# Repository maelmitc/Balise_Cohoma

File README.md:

# $${\color{black}Balise \space \color{black}Cohoma}$$

* CHARBONNIER Maëna
* MITCHEL Maël
* NGUYEN Denis
* SALOT Robin
* TESTUZ Lauriane

## $${\color{black}Présentation \space \color{black}du \space \color{black}{projet}}$$

Ce projet est en collaboration avec des deuxièmes années qui participent au projet Cohoma, pour l'armée de terre. Ce projet
est une compétition entre différentes écoles d'ingénieurs. Il consiste en la création d'un robot autonome s'adaptant à tout type de terrains. Ce robot doit lâcher des balises sur son chemin, elles ont pour but de le localiser. C'est ce sur quoi nous avons travaillé. 
   
Une LED RGB est utilisée afin de montrer le niveau de batterie de la balise (vert: pleine charge, jaune: à moitié chargée et rouge: déchargée). Quatre LEDs bleues sont également utilisées afin de déterminer le niveau de connexion Internet de la balise. Il y a également un capteur infrarouge qui permet de communiquer avec le rover afin d'allumer la batterie. Enfin, on utilise un convertisseur Buck-Boost, qui est une alimentation à découplage qui convertit une tension continue en une autre tension continue de plus faible ou de plus grande valeur, mais de polarité inverse.

## $${\color{black}Cahier \space \color{black}des \space \color{black}{charges}}$$

* Rendre visible le niveau de batteries de la balise (sur la balise).
* Rendre visible le niveau de réception WIFI de la balise (sur la balise).
* Communication infrarouge entre une télécommande et la balise.
* Communication infrarouge entre le rover et la balise dans le but d'allumer la balise après lors de l'éjection.
* Alimenter la balise.

## $${\color{black}Datasheet}$$

* [Buck / Boost ](https://www.farnell.com/datasheets/1999134.pdf)
* [Diode (Buck) (1N4148)](https://4donline.ihs.com/images/VipMasterIC/IC/DIOD/DIOD-S-A0001754954/DIOD-S-A0001754954-1.pdf?hkey=6D3A4C79FDBF58556ACFDE234799DDF0)
* [Diode Schottky (FSV340AF)](https://www.mouser.fr/datasheet/2/308/FSV340AF_D-1810142.pdf)
* [Capteur IR TFBS4650](https://www.vishay.com/docs/84672/tfbs4650.pdf)
* [Interface USB/UART(CY7C64225-28PVXCT)](https://www.mouser.fr/datasheet/2/196/CYPR_S_A0003298042_1-3003715.pdf)
* [Encodeur/Decodeur IrDA MCP2120-I/SL ](https://docs.rs-online.com/4edb/0900766b814ada76.pdf)
* [Quartz pour Encodeur/Decodeur IrDA ABLS-7.3728MHZ-20-B-3-H-T ](https://www.mouser.fr/datasheet/2/3/abls-1664338.pdf)
* [Récepteur IrDA TSOP75338TT](https://www.mouser.fr/datasheet/2/427/tsop753-1767096.pdf)
* [Emetteur IrDA VSML3710-GS18](https://www.mouser.fr/datasheet/2/427/vsml3710-1766511.pdf)
* [Processeur STM32L412KBT6](https://www.mouser.fr/datasheet/2/389/stm32l412c8-1851177.pdf)
* [Quartz pour STM32 ABLS-16.000MHZ-20-B-3-H-T:](https://www.mouser.fr/datasheet/2/3/abls-1664338.pdf)
* [Led bleu (niveau de réception) : MP008276]( https://www.farnell.com/datasheets/3497873.pdf)
* [Led RGB (niveau batterie) : 5988G10313F ](https://www.mouser.fr/datasheet/2/109/C18481B-2944388.pdf)
* [Driver de LED I2C : PCA9685PW,118 ]( https://www.mouser.fr/datasheet/2/302/PCA9685-1127478.pdf)

## $${\color{black}Déroulement \space \color{black}du \space \color{black}{projet}}$$

### Software :

L'objectif du logiciel développé est le traitement des données du routeur et de la batterie et la commande du <em>driver</em> LED. Le code a été développé en C. Le code est implémenté sur un processeur STM32 L412KBT6. En fonction des données reçues, le logiciel commande les LEDs, en particulier en fonction du niveau de batterie disponible. Le driver de LEDs, relié à quatre LEDs bleues et une LED RGB est connecté en I2C avec le processeur STM32.

* [Architecture <em>software</em>](Software/[CoHoMa]BeaconSoftwareArchitecture.drawio) (originale, modifiée depuis)
* [Code](Software/CHMBeaconB.zip)

#### Batterie
Selon le niveau de batterie calculé, 1 à 4 Blue LEDs sont allumées
* 75% : 4 LEDs activées
* 50% : 3 LEDs activées
* 25% : 2 LEDs activées
* 10% : 1 LED activée
On utilise une connexion I²C pour lier le STM32 au <em>driver</em> LED.

#### Routeur/IR
On utilise une LED RGB pour témoigner de la qualité de la connexion.
En fonctionnement normal, on utilise 3 couleurs : rouge (signal faible), vert (signal moyen), bleu (signal fort).

#### Problèmes rencontrés lors du développement :
* Longue lecture des fiches techniques des composants utilisés
* Recherche et étude d'un algorithme pour déterminer le niveau de batterie (SOC Algorithm)
* Lien entre la partie <em>hardware</em> et <em>software</em>, en particulier le lien avec la batterie/le niveau de charge

D'un point de vue personnel, je juge avoir sous-estimé la quantité de travail à fournir dans la partie <em>software</em>, trop importante pour une seule personne.

### Hardware - PCB Leds:

La version finale de mon [PCB](Hardware/PCB_LEDs/PCB_LEDs.kicad_sch_copie.kicad_pro).

#### Composants utilisés : 

Type de produit | Empreinte | Nombre 
--- | --- | ---
Driver de LEDs | Package_STO:TSSOP-28_4.4x9.7mm_P0.65mm | 1
LED bleue | LED_SMD:LED_0603_1608Metric_Pad1.05x0.95mm_HandSolder | 4 
LED RGB | LED_SMD:LED_Avago_PLCC6_3x2.8mm | 1
Résistance (100Ω et 150Ω)| Resistor_SMD:R_0603_1608Metric_Pad0.98x0.95mm_HandSolder | 7
Connecteur 01x05 | Connector_JST:JST_XH_B5B-XH-A_1x05_P2.50mm_Vertical | 1

#### Utilité des composants :

* Driver de LEDs : pilote les LEDs.
* LEDs bleues : montrent le niveau de connexion Wifi sur la balise. Plus le nombre de LEDs allumées est important, plus la connexion internet est bonne. 
* LED RGB : montre le niveau de batterie de la balise. Si la LED est verte, la balise est entièrement chargée ; jaune, à moitié chargée ; rouge, déchargée.
* Résistances : permettent de limiter le courant qui traverse les LEDs.
* Connecteur : permet de faire communiquer le driver de LEDs avec l’extérieur. Il est composé de cinq sorties : une d'alimentation et une de masse, mais également d'une sortie SDA (Serial Data Line), d'une sortie SCL (Serial Clock Line) et d'une sortie output enable, qui permet d’activer ou de désactiver les sorties de LEDs, en fonction des besoins.

#### Choix des résistances : 

Le driver de LEDs est alimenté par une tension de 5V. La tension maximum que peuvent recevoir les LEDs est d’environ 3V. Or, puisqu’on a un courant de 25 mA qui doit traverser les LEDs, on en conclut que la résistance qui doit être ajoutée afin de limiter la tension est de 100Ω. EN ce qui concerne la LED RGB, la diode rouge supporte une tension moins importante que les diodes jaune et verte. Sa résistance doit donc être supérieure à celles des diodes jaune et verte. C’est pourquoi, on ajoute une résistance de 150Ω.

#### Problèmes rencontrés lors de la fabrication de ce PCB : 

En ce qui concerne les LEDs bleues, il n'y a pas de problème, elles s'allument correctement. En revanche, cette partie comporte un principal problème : à cause d'une mauvaise connexion des pins de la LED RGB, on s'est rendu compte que seule la diode verte s'allume, les diodes jaune et rouge ne fonctionnent pas. Il faut prendre garde à ne pas se tromper entre l'anode et la cathode des diodes, pour éviter que l'erreur ne se reproduise. 

### Hardware - PCB IR :

La version finale de mon [PCB](Hardware/PCB_IR/cohoma.kicad_pro).

#### Composants utilisés : 

Type de produit | Empreinte | Nombre 
--- | --- | ---
Décodeur | Package_SO:SOIC-14_3.9x8.7mm_P1.27mm | 1
Récepteur Infrarouge | Package_SO:TSOP753TT (empreinte que nous avons créée) | 1
Quartz | Crystal:Crystal_SMD_7050-2Pin_7.0x5.0mm | 1
Condensateur (20 pF et 100 nF)| Capacitor_SMD:C_0603_1608Metric_Pad1.08x0.95mm_HandSolder | 3
Connecteur 01x03 | Connector_PinHeader_1.27mm:PinHeader_1x03_P1.27mm_Horizontal | 1 

Ce PCB se compose de plusieurs parties:

#### Récepteur IR:
Le récepteur IR reçoit un signal provenant d'un émetteur IR. Il renvoie alors RXIR à l'encodeur/décodeur dans le but que le signal soit décodé.
Afin d'éviter les fluctuations de tensions, il était recommandé par la datasheet, lorsque Vs<2.8 V d'utiliser une résistance et un condensateur. Ce n'est ici pas le cas, cependant, afin d'éviter tout risque, un condensateur de 100 nF a tout de même été ajouté.

#### Encodeur/Décodeur:
Dans le cadre de ce projet, ce composant a été utilisé uniquement comme un décodeur. Il reçoit RXIR, le décode et renvoie UART_RX au microcontrôleur (via le connecteur).
En effet, pour être compris par le microcontrôleur, le signal doit être en UART.

Les "BAUD" permettent de modifier la vitesse de transmission. Ils sont tous les trois mis à la masse ici, ce qui équivaut à les mettre à 0.

#### Quartz:
Le quartz sert d'horloge. Il est ici accompagné de deux condensateurs qui permettent de "lisser" afin que l'horloge soit vraiment régulière.

#### Difficultés rencontrées lors de la fabrication de ce PCB :
* Trouver les schematics correspondants au projet (pour plusieurs composants, elles n'existaient pas sur Kicad: il a donc été nécessaire de les trouver, les télécharger, puis les importer sur Kicad).
* La datasheet du quartz ne permettait pas de connaître la schematic associée, il fallait effectuer d'autres recherches.
* De même pour les empreintes de certains composants, il fallait alors trouver une empreinte très proche, ou bien créer l'empreinte dans certains cas.
* Rendre le PCB le plus petit possible tout en respectant une contrainte: les deux condensateurs associés au Quartz devaient être aussi proche que possible de ce dernier.
* Problèmes rencontrés lors de la soudure liés à une mauvaise empreinte ( qui a été corrigée sur la dernière version du PCB).

### Hardware - PCB Buck-Boost:

La version finale de notre [PCB](Hardware/PCB_BuckBoost/pcb_v3/pcb_v3.kicad_pro).

#### Composants utilisés : 

Type de produit | Empreinte | Nombre 
--- | --- | ---
Diode| Diode_SMD:D_SOD-123F | 1
Diode| Diode_SMD:D_SOD-323F | 1
PS1| Footprints_Balise:PS1 | 1
Régulateur Buck/Boost | Package_SO:SOIC-8-1EP_3.9x4.9mm_P1.27mm_EP2.29x3mm | 2
Condensateur polarisé (330 uF)| Capacitor_SMD:CP_Elec_10x10.5 | 2
Condensateur polarisé (100 uF)| Capacitor_SMD:CP_Elec_6.3x7.7 | 1
Condensateur polarisé (22 uF)| Capacitor_SMD:CP_Elec_5x5.4 | 1
Condensateur (2.2 uF, 1 uF et 0.47 nF)| Capacitor_SMD:C_0603_1608Metric_Pad1.08x0.95mm_HandSolder | 6
LED bleue | LED_SMD:LED_0603_1608Metric_Pad1.05x0.95mm_HandSolder | 4 
Inductance (100 uH)| Inductor_SMD:L_Wuerth_WE-PD-Typ-LS | 2
Résistance | Resistor_SMD:R_0603_1608Metric_Pad0.98x0.95mm_HandSolder | 11
Diode Schottky | Footprints_Balise:Diode_Schottky (empreinte créée)| 2
Connecteur 01x02 | Connector_JST:JST_XH_B2B-XH-A_1x02_P2.50mm_Vertical | 4

#### Utilité des composants
* LEDs bleues : témoignent du bon fonctionnement de l'alimentation
* Diodes / Diode Schottky : permettent les différents états de commutation du régulateur
* Régulateur à découpage : gère le découpage (via le rapport cyclique) de la tension en fonction des différents états. Les régulateurs sont au nombre de deux, chacun est monté différemment, permettant le passage au mode Buck ou Boost.
* PS1 : régule la tension

#### Choix des composants     
Les composants (autre que ceux imposés) ont été sélectionnés en fonction des datasheets des montages Buck et Boost et des composants passifs disponibles à l'ENSEA. Pour ce qui est des condensateurs, des condensateurs classiques ou polarisés ont été choisi en fonction de la valeur des capacités indiquées sur la datasheet (au dessus de 10 uF, on choisit un condensateur polarisé).

#### Explication du fonctionnement des régulateurs à découplage  
Un régulateur de découplage est un type de régulateur de tension qui utilise des composants électroniques commutés (transistors, inductances, condensateurs) pour convertir l'énergie de manière efficace. 

Régulation de la tension d'entrée : Le régulateur de découplage commence par réguler et contrôler la tension d'entrée, celle-ci pouvant être supérieure ou inférieure à la tension de sortie souhaitée, à l'aide de composants électroniques commutés.

Conversion d'énergie : L'énergie est efficacement convertie en utilisant un interrupteur électronique, généralement un transistor, pour commuter rapidement entre les états "on" et "off". Il est possible de réduire les pertes d'énergie et d'améliorer l'efficacité globale du régulateur grâce à cette commutation.

Stockage de l'énergie : Pendant la commutation, l'énergie est stockée dans une inductance (bobine) lors de l'état "on" de l'interrupteur et est libérée lors de l'état "off". Cela permet de réguler et de maintenir la tension de sortie constante malgré les variations de la tension d'entrée ou de la charge.

Filtrage : Le régulateur de découplage utilise également des condensateurs pour filtrer les fluctuations résiduelles de la tension de sortie et pour fournir une alimentation stable et régulée.

#### Difficultés rencontrées lors de la fabrication de ce PCB : 
* Repérer sur la datasheet les montages buck et boost qui correspondaient au projet.
* Choisir des empreintes des condensateurs et des inductances adaptées à la situations (exemple : condensateurs polarisés).
* Assigner (voire créer) les bonnes empreintes car elles n'étaient pas toujours disponibles sur Kicad.  
* Agencer les composants afin d'obtenir un PCB le plus petit possible.
* Placer les composants traversés par une forte tension de manière optimale (ils devaient être proches des régulateurs à découpage).
* Il fallait imposer un courant de sortie de 100 mA, ce qui n'était possible que si la balise était complète. Or, ce n'était pas le cas, puisque nous n'avions que le PCB. Nous avons donc dû rajouter deux résistances en parallèle à un condensateur polarisé.
* Choisir une largeur de piste suffisante en fonction du courant qui traversait les différents composants. 
* Augmenter le nombre de vias car ils ne fonctionnaient pas toujours.
* Certaines pastilles de cuivres n'étaient pas connectés à la masse, une erreur lors de la conception du PCB sur Kicad.

## $${\color{black}Impact \space \color{black}environnemental}$$

### $${\color{green}Expliquer \space \color{green}les \space \color{green}{critères} \space \color{green}de \space \color{green}choix \space \color{green}du \space \color{green}mode \space \color{green}d'alimentation \space \color{green}de \space \color{green}votre \space \color{green}{projet}}$$

Notre projet exigeait déjà un cahier des charges précis à respecter. En effet, la plupart des composants, y compris l'alimentation Buck-Boost, étaient imposés. Cependant, on peut tout de même se demander pourquoi c'est une alimentation à découpage qui à été choisie plutôt qu'une alimentation linéaire. En effet, l'alimentation à découpage possède un rendement bien plus élevé (et consomme donc moins d'énergie) que l'amplificateur linéaire grâce à son fonctionnement "alterné" entre différents états de commutations. Cette meilleure efficacité énergétique est principalement due à leur principe de fonctionnement différent. Dans un régulateur linéaire, la tension excédentaire est dissipée sous forme de chaleur par un transistor de régulation. Cela signifie que la différence de tension entre l'entrée et la sortie du régulateur est convertie en chaleur, ce qui entraîne une perte d'énergie importante. Par conséquent, les régulateurs linéaires ont généralement une efficacité relativement faible, en particulier lorsque la différence de tension entre l'entrée et la sortie est importante. 

En revanche, les régulateurs de découplage utilisent des composants électroniques commutés, tels que des transistors MOSFET et des inductances, pour réguler la tension de sortie. Ces composants commutent rapidement entre les états "on" et "off", ce qui permet de minimiser les pertes d'énergie. Lorsque le transistor est en état "on", il présente une résistance très faible, ce qui réduit les pertes de puissance. Lorsque le transistor est en état "off", l'inductance stocke l'énergie et la restitue lors de l'état "on" suivant, ce qui permet de maintenir une tension de sortie constante.En conséquence, les régulateurs de découplage ont une efficacité énergétique beaucoup plus élevée que les régulateurs linéaires. Une plus grande quantité d'énergie est transférée du côté de l'entrée vers le côté de la sortie sans être dissipée sous forme de chaleur. De plus, en raison du rapport cyclique, le transformateur à l'intérieur de l'alimentation peut être très petit, réalisant ainsi la miniaturisation de la taille de l'alimentation tout en permettant également l'utilisation normale de l'alimentation. 

Il est à noter que dans certains cas (dans d'autres projets par exemple), l'utilisation des régulateurs linéaire est préférable : 
* Moins sensible aux variations de la tension d'entrée,
* Coût moins élevé,
* Meilleure performance en terme de réduction de bruit et des interférences électromagnétique, 
* Moins complexe
* Réglage plus fin de la sortie.

### $${\color{green}Votre \space \color{green}projet \space \color{green}favorise-t-il \space \color{green}une \space \color{green}utilisation \space \color{green}judicieuse \space \color{green}et \space \color{green}rationnelle \space \color{green}de \space \color{green}l'énergie, \space \color{green}en \space \color{green}minimisant \space \color{green}{les}}$$

### $${\color{green}impacts \space \color{green}de \space \color{green}sa \space \color{green}production, \space \color{green}de \space \color{green}sa \space \color{green}distribution \space \color{green}et \space \color{green}de \space \color{green}sa \space \color{green}{consommation?}}$$
 
La plupart des composants étant imposés, nous avons eu peu de marge de manoeuvre. Nous avons donc porté une attention toute particulière à la taille des PCBs conçus. En effet, ces derniers devaient être les plus petits possibles, afin de ne pas gaspiller de matériaux. De plus, les PCBs ayant été réalisés sur place, leur impact environnemental dû aux transports était minime, les composants étant déjà à l'école.
 
Pour ce qui est des LEDs présentes sur le projet, elles ne s’allument que lorsque le module qui leur est associé est sollicité. Ainsi il n'y a pas d'énergie utilisée inutilement. De plus, nous nous sommes assurés qu’aucun composant ne consomme plus d’énergie que celle nécessaire à son bon fonctionnement.

Cependant, si l’on s’intéresse au projet de manière plus large, son impact est plus important que ce que nous avons décrit précédemment. En effet, plusieurs écoles sont en compétition dans la réalisation de ce projet pour ne sélectionner que le meilleur. L’impact aurait été moins important si une seule équipe d’ingénieurs professionnels s’en était chargée. Néanmoins, cette compétition entre écoles encourage chacun des participants à réaliser le projet le plus efficace et propre possible dans l’espoir d’être sélectionnés.

## $${\color{black}Conclusion}$$

Nous avons manqué de temps pour atteindre tous nos objectifs. Cependant, si nous pouvions donner des conseils à nos successeurs, nous dirions de :
 
* Bien lire les datasheet des composants, de façon à choisir des valeurs de résistances ou de condensateurs appropriées, par exemple. 
* Faire particulièrement attention aux empreintes, quitte à en créer, de façon à n'avoir aucun problème lors de la soudure.
* Faire particulièrement attention au sens des diodes, ne pas intervertir l'anode et la cathode, dans le cas ou le PCB en comporte.
* Faire attention à la largeur des pistes, en fonction du courant qui traverse les différents composants.

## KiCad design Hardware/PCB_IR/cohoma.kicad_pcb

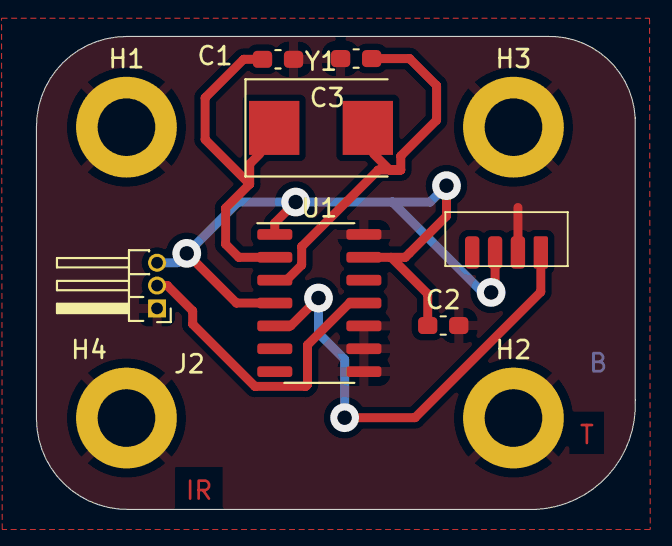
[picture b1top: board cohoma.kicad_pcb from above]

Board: 2 copper layers, 33.3 x 26.3 mm, 11 parts (0 on the bottom side), 5 nets.

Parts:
C1, C3: 20 pF; C_0603_1608Metric_Pad1.08x0.95mm_HandSolder
C2: 100 nF; C_0603_1608Metric_Pad1.08x0.95mm_HandSolder
H1: Mounting Hole 1; MountingHole_3.2mm_M3_DIN965_Pad
H2: Mounting Hole 2; MountingHole_3.2mm_M3_DIN965_Pad
H3: Mounting Hole 3; MountingHole_3.2mm_M3_DIN965_Pad
H4: Mounting Hole 4; MountingHole_3.2mm_M3_DIN965_Pad
J2: Conn_01x03; PinHeader_1x03_P1.27mm_Horizontal
U1: MCP2120-I/P; SOIC-14_3.9x8.7mm_P1.27mm
U2: TSOP75338WTT; TSOP753TT
Y1: ABLS-7.3728MHz-20-B-3-H-T; Crystal_SMD_7050-2Pin_7.0x5.0mm

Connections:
+3.3V: C2.1, J2.3, U1.1 (VDD), U1.4 (*RESET), U1.13 (EN)
GND: C1.2, C2.2, C3.2, H1.1, H2.1, H3.1, H4.1, J2.1, U1.8 (BAUD2), U1.9 (BAUD1), U1.10 (BAUD0), U1.14 (VSS)
Q_IN: C1.1, U1.2 (OSC1/CLKIN), Y1.1
Q_OUT: C3.1, U1.3 (OSC2), Y1.2
UART_RX: J2.2, U1.11 (RX)

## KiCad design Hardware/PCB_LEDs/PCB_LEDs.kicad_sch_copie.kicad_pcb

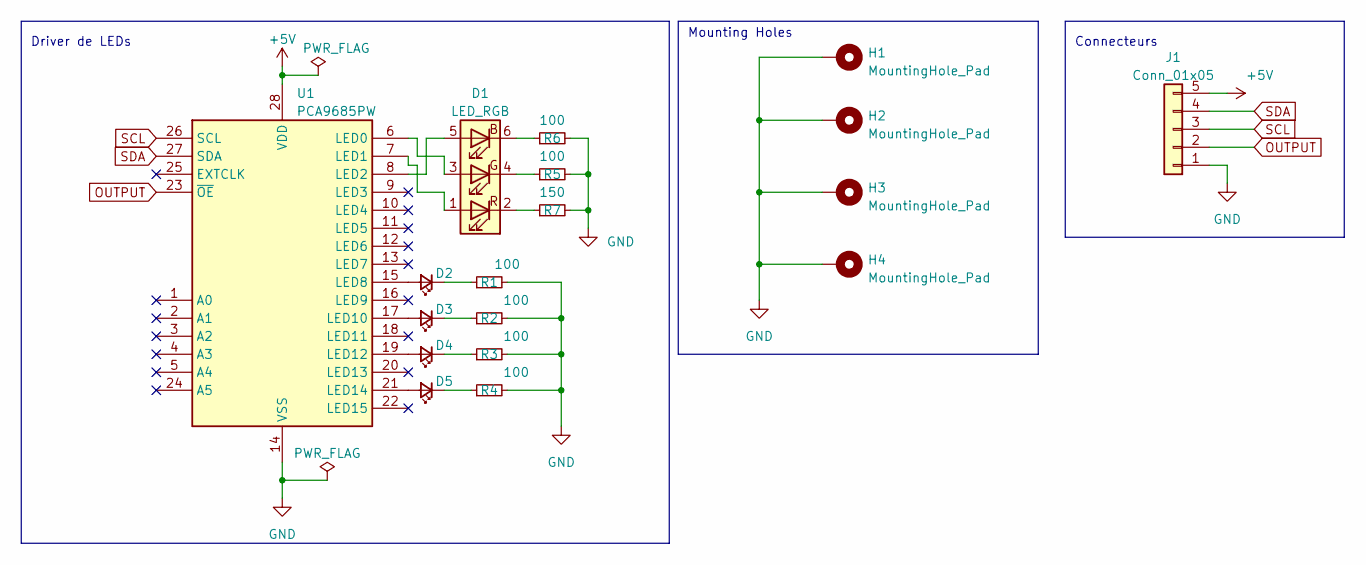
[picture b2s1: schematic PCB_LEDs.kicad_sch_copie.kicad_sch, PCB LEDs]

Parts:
D1: LED_RGB; LED_Avago_PLCC6_3x2.8mm
D2: LED_1; LED_0603_1608Metric_Pad1.05x0.95mm_HandSolder
D3: LED_2; LED_0603_1608Metric_Pad1.05x0.95mm_HandSolder
D4: LED_3; LED_0603_1608Metric_Pad1.05x0.95mm_HandSolder
D5: LED_4; LED_0603_1608Metric_Pad1.05x0.95mm_HandSolder
H1, H2, H3, H4: MountingHole_Pad; MountingHole_3.2mm_M3_DIN965_Pad
J1: Conn_01x05; JST_XH_B5B-XH-A_1x05_P2.50mm_Vertical
R1, R2, R3, R4, R5, R6: 100; R_0603_1608Metric_Pad0.98x0.95mm_HandSolder
R7: 150; R_0603_1608Metric_Pad0.98x0.95mm_HandSolder
U1: PCA9685PW; TSSOP-28_4.4x9.7mm_P0.65mm

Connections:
+5V: J1.5, U1.28 (VDD)
GND: H1.1, H2.1, H3.1, H4.1, J1.1, R1.2, R2.2, R3.2, R4.2, R5.2, R6.2, R7.2, U1.14 (VSS)
unnamed: D1.5 (BA), U1.8 (LED2)
unnamed: D1.4 (GK), R5.1
unnamed: D1.6, R6.1
unnamed: D1.1 (RA), U1.7 (LED1)
unnamed: D1.2 (RK), R7.1
unnamed: D2.2 (A), U1.15 (LED8)
unnamed: D2.1 (K), R1.1
unnamed: D3.2 (A), U1.17 (LED10)
unnamed: D3.1 (K), R2.1
unnamed: D4.2 (A), U1.19 (LED12)
unnamed: D4.1 (K), R3.1
unnamed: D5.2 (A), U1.21 (LED14)
unnamed: D5.1 (K), R4.1
unnamed: D1.3 (GK), U1.6 (LED0)
OUTPUT: J1.2, U1.23 (~OE)
SCL: J1.3, U1.26 (SCL)
SDA: J1.4, U1.27 (SDA)

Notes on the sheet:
Connecteurs
Mounting Holes
Driver de LEDs

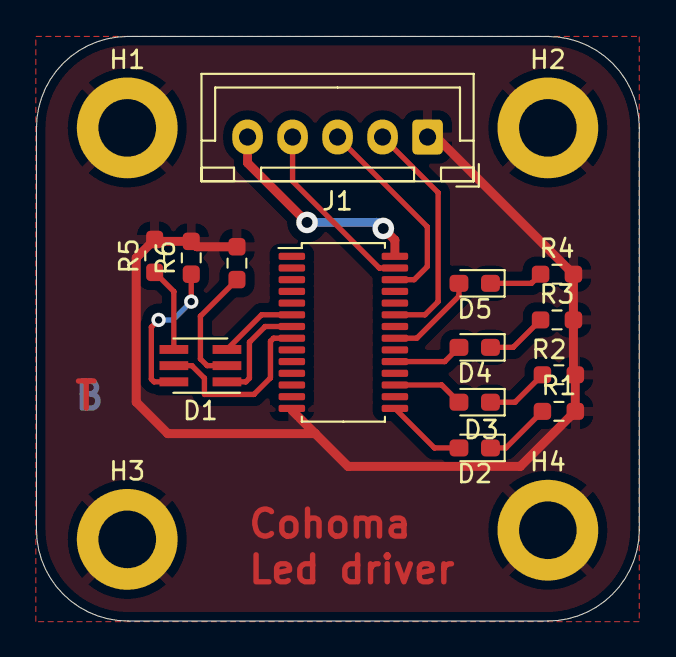
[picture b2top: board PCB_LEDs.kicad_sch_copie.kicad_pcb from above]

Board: 2 copper layers, 33.5 x 32.5 mm, 18 parts (0 on the bottom side), 19 nets.

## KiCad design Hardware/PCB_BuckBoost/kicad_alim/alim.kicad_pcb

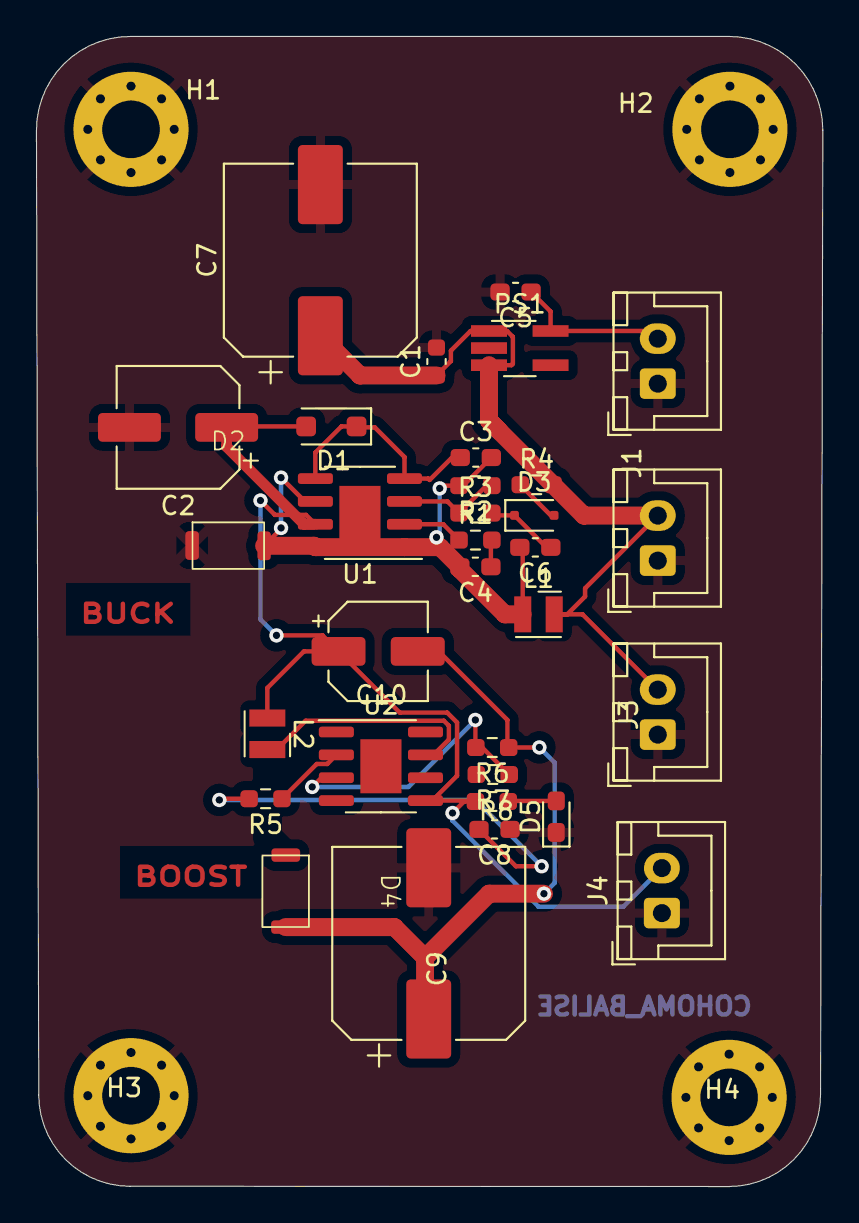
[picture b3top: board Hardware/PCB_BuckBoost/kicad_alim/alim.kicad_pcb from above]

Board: 2 copper layers, 43.7 x 63.9 mm, 36 parts (0 on the bottom side), 16 nets.

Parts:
C1: 0.47u; C_0603_1608Metric
C2: 100uF; CP_Elec_6.3x7.7
C3: 2.2 µF; C_0603_1608Metric_Pad1.08x0.95mm_HandSolder
C4, C6: 1 µF; C_0603_1608Metric_Pad1.08x0.95mm_HandSolder
C5: 0.47u; C_0603_1608Metric_Pad1.08x0.95mm_HandSolder
C7: 330uF; CP_Elec_10x10.5
C8: 1µF; C_0603_1608Metric_Pad1.08x0.95mm_HandSolder
C9: 470uF; CP_Elec_10x10.5
C10: 22uF; CP_Elec_5x5.4
D1: 1N4148; D_SOD-123F
D2, D4: FSV330AF; Diode_Shottky (copy)
D3: 1N4148; D_SOD-323F
D5: LED; LED_0603_1608Metric_Pad1.05x0.95mm_HandSolder
H1, H2, H3, H4: MountingHole_Pad; MountingHole_3.2mm_M3_Pad_Via
J1, J2, J3, J4: Conn_01x02; JST_XH_B2B-XH-A_1x02_P2.50mm_Vertical
L1: 100 µH; L_Wurth_WE-LQSH-2512
L2: 27 µH; L_Wurth_WE-LQSH-2512
PS1: BU33SD5WG-TR; TSOT-23-5_HandSoldering
R1: 470; R_0603_1608Metric_Pad0.98x0.95mm_HandSolder
R2: 1.2 k; R_0603_1608Metric_Pad0.98x0.95mm_HandSolder
R3: 3.7k; R_0603_1608Metric_Pad0.98x0.95mm_HandSolder
R4: 10Ω; R_0603_1608Metric_Pad0.98x0.95mm_HandSolder
R5, R8: 1k; R_0603_1608Metric_Pad0.98x0.95mm_HandSolder
R6: 10.7; R_0603_1608Metric_Pad0.98x0.95mm_HandSolder
R7: 1.24k; R_0603_1608Metric_Pad0.98x0.95mm_HandSolder
U1, U2: MIC3172YM; SOIC-8-1EP_3.9x4.9mm_P1.27mm_EP2.29x3mm

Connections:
+3.3V: C5.1, J1.2, PS1.5 (VOUT)
+5V: C1.1, C7.1, J2.2, J3.2, L1.2, PS1.1 (VIN), PS1.3 (STBY), R4.2
+15V: C2.1, C10.1, D1.2 (A), J4.2, L2.1, R8.1, U1.7 (VSW), U2.5 (VIN)
GND: C1.2, C2.2, C5.2, C7.2, C8.1, C9.2, D2.2 (A), D5.1 (K), H1.1, H2.1, H3.1, H4.1, J1.1, J2.1, J3.1, J4.1, PS1.2 (GND), R7.2, U2.1 (SGND), U2.6 (PGND2), U2.8 (PGND1)
unnamed: C4.1, R1.2
unnamed: C8.2, R5.2
unnamed: C3.1, D1.1 (K), U1.4 (SYNC/EN), U1.5 (VIN)
unnamed: C3.2, C4.2, C6.2, D2.1 (K), L1.1, R1.1, R2.2, U1.1 (SGND), U1.2 (COMP), U1.6 (PGND2), U1.8 (PGND1), U1.9
unnamed: D3.2 (A), R4.1
unnamed: C6.1, D3.1 (K), R3.2
unnamed: D4.2 (A), L2.2, U2.7 (VSW)
unnamed: D5.2 (A), R8.2
unnamed: R2.1, R3.1, U1.3 (FB)
unnamed: R5.1, U2.2 (COMP)
unnamed: R6.2, R7.1, U2.3 (FB)
Routeur: C9.1, C10.2, D4.1 (K), R6.1

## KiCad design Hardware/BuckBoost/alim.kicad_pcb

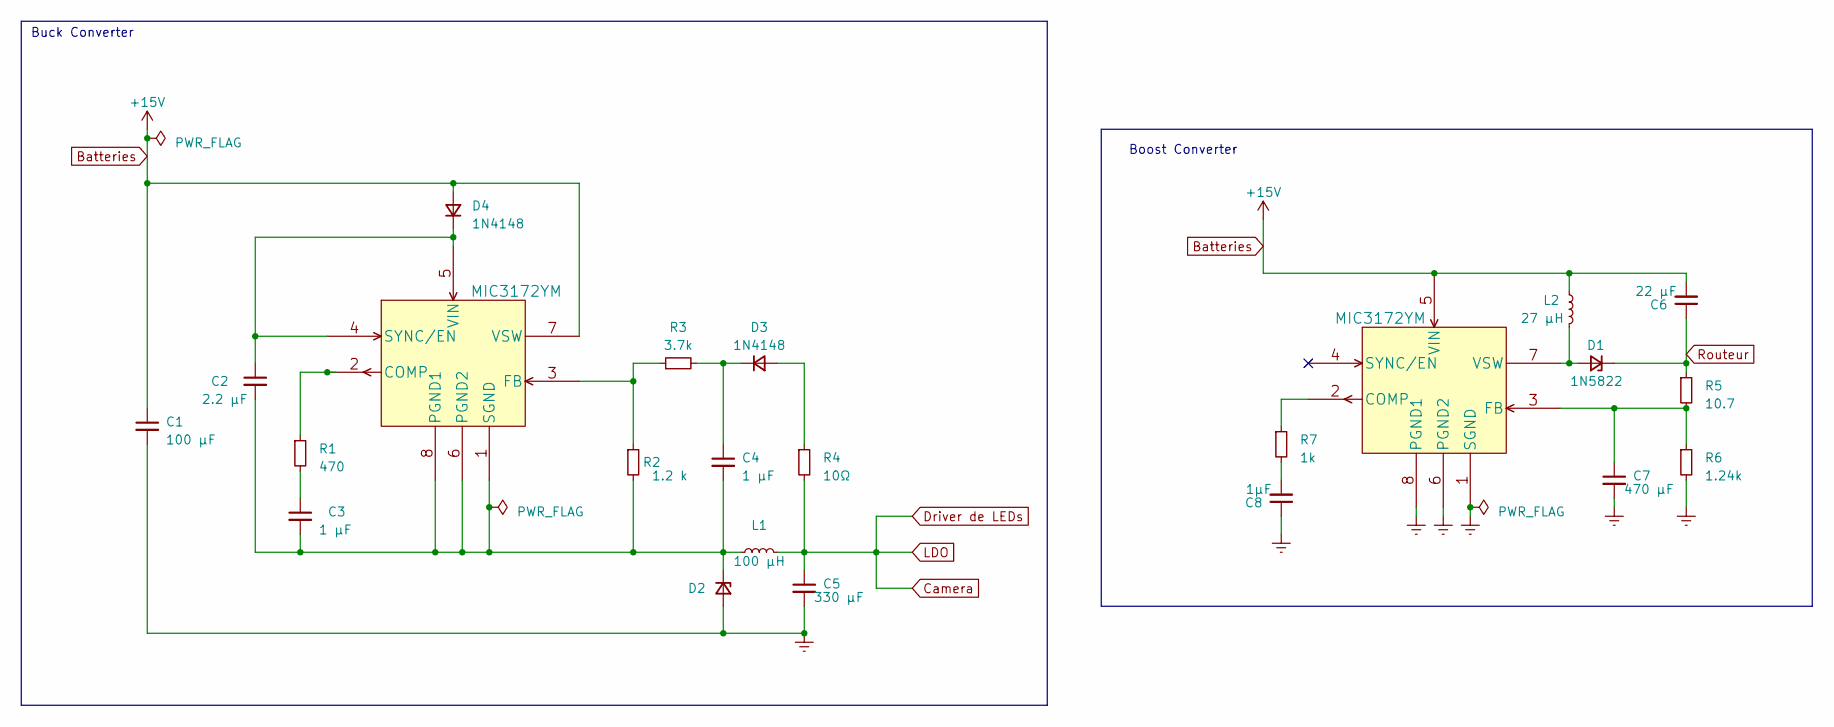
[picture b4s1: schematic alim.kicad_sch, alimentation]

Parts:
C1: 100 µF; C_0603_1608Metric_Pad1.08x0.95mm_HandSolder
C2: 2.2 µF; C_0603_1608Metric_Pad1.08x0.95mm_HandSolder
C3, C4: 1 µF; C_0603_1608Metric_Pad1.08x0.95mm_HandSolder
C5: 330 µF; C_0603_1608Metric_Pad1.08x0.95mm_HandSolder
C6: 22 µF; C_0603_1608Metric_Pad1.08x0.95mm_HandSolder
C7: 470 µF; C_0603_1608Metric_Pad1.08x0.95mm_HandSolder
C8: 1µF; C_0603_1608Metric_Pad1.08x0.95mm_HandSolder
D1: 1N5822; DIOAD2120W130L950D530P
D2: D_Zener_Small; TO-277
D3, D4: 1N4148; SOD2513X120N
L1: 100 µH; L_0805_2012Metric_Pad1.05x1.20mm_HandSolder
L2: 27 µH; L_0805_2012Metric_Pad1.05x1.20mm_HandSolder
R1: 470; R_0603_1608Metric_Pad0.98x0.95mm_HandSolder
R2: 1.2 k; R_0603_1608Metric_Pad0.98x0.95mm_HandSolder
R3: 3.7k; R_0603_1608Metric_Pad0.98x0.95mm_HandSolder
R4: 10Ω; R_0603_1608Metric_Pad0.98x0.95mm_HandSolder
R5: 10.7; R_0603_1608Metric_Pad0.98x0.95mm_HandSolder
R6: 1.24k; R_0603_1608Metric_Pad0.98x0.95mm_HandSolder
R7: 1k; R_0603_1608Metric_Pad0.98x0.95mm_HandSolder
U2, U4: MIC3172YM; SOIC127P600X175-8N

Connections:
Batteries: C1.1, C6.2, D4.2 (A), L2.1, U2.5 (VIN), U4.7 (VSW)
Camera: C5.1, L1.2, R4.2
Earth: C1.2, C5.2, C7.2, C8.1, D2.2 (A), R6.2, U2.1 (SGND), U2.6 (PGND2), U2.8 (PGND1)
unnamed: C2.2, C3.2, C4.2, D2.1 (K), L1.1, R2.2, U4.1 (SGND), U4.6 (PGND2), U4.8 (PGND1)
unnamed: C3.1, R1.2
unnamed: C8.2, R7.2
unnamed: D1.2 (A), L2.2, U2.7 (VSW)
unnamed: D3.2 (A), R4.1
unnamed: C4.1, D3.1 (K), R3.2
unnamed: C2.1, D4.1 (K), U4.4 (SYNC/EN), U4.5 (VIN)
unnamed: R7.1, U2.2 (COMP)
unnamed: C7.1, R5.2, R6.1, U2.3 (FB)
unnamed: R1.1, U4.2 (COMP)
unnamed: R2.1, R3.1, U4.3 (FB)
Routeur: C6.1, D1.1 (K), R5.1

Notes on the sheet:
Buck Converter
Boost Converter

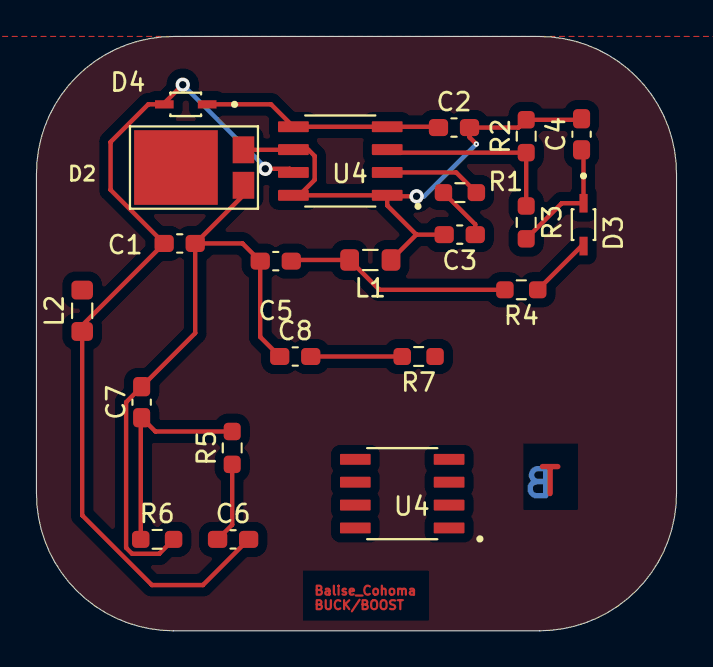
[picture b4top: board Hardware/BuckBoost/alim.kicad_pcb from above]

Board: 2 copper layers, 35.6 x 33.0 mm, 22 parts (0 on the bottom side), 13 nets.

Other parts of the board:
U4#2: MIC3172YM; SOIC127P600X175-8N

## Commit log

2023-04-11 Added Untitled Diagram.drawio
2023-04-15 schema Kicad des montages Buck et Boost
2023-04-16 Modifs des conflits
    Il y avait des éléments qui avaient les mêmes noms dans le buck et dans le boost du coup ça causait des erreurs
2023-04-16 Correction des autres erreurs
2023-04-16 Ajouts des autres fichiers
2023-04-16 Footprint assignée
    Je suis vraiment pas sur pour la diode Shottky
2023-04-16 PCB Boost
    J'ai essayer d'avoir le moins le fils longs possible
2023-04-16 FIN PCB BOOST
    Normalement jme suis occupé de l'association de tous les composants et je t'ai fait de la place sur la partie basse du PCB pour le buck
    Hésite pas a modifié la taille ou d'autres truc si ça te convient mieux
2023-04-16 Create Cahier des charges
2023-04-16 Footprints des diodes à importer
2023-04-16 Create o
2023-04-16 Routage de la partie Boost incomplet car il y a un problème avec les librairies de la diode et du MIC, à reprendre depuis un ordinateur de l'Ensea
2023-04-17 Add files via upload
    Software Architecture (C/Assembly)
2023-04-17 Complete Software Architecture
    Beacon Software Architecture in C/Assembly (Including the use of interrupts and flags)
2023-04-17 PCB BOOST + RectifIcation FOOTPRINTS
    Je ne suis toujours pas sur des footprints surtout pour la diode D1
2023-04-17 PCB_IR
2023-04-17 pcb revue
2023-04-17 PCB IR
2023-04-17 PCB IR (le bon)
2023-04-17 ouais
2023-04-17 Réorganisation
2023-04-17 Correction des erreurs après amphi
2023-04-17 PPZ m'as aidé
2023-05-01 renommage des datasheets et assignation d'empreintes du Buck/Boost
2023-05-01 composants ps1 associé
2023-05-01 Update PCB
2023-05-01 mise au propre fichier PCB_BuckBoost et début du routage
2023-05-01 Repush
2023-05-01 pcb presque terminé (3 erreurs)
2023-05-02 j'ai corrigé les erreurs dans le pcb
2023-05-09 essai
2023-05-09 changement du schéma Buck/Boost car erreur
2023-05-09 essai2
2023-05-09 PCB avec titre
2023-05-09 Footprint Diode Shottky
2023-05-09 assignation d'empreintes
2023-05-09 Test
2023-05-09 Réparé ?
2023-05-09 Est ce que ca va marcher sur le pc de Maël ?
2023-05-09 début du routage pcb
2023-05-09 autosave
2023-05-09 routage pcb
2023-05-09 routage Buck quasi terminé
2023-05-09 PCB BUCK/BOOST
2023-05-15 add board buck boost
2023-05-15 version finale
2023-05-15 Version vraiment finale
2023-05-15 PCB Final en avancement
2023-05-16 PCB presque fini (manque les liaisons)
2023-05-16 Correction erreurs V2
2023-05-22 pcb v1 buck boost
2023-05-22 PCB V3 presque fini (il manque quelques tracks)
2023-05-23 PCB_VB (il reste une erreur au niveau du F.cu)
2023-05-23 PCB V3 fini
2023-05-23 pcb sans erreurs (mais avec track à 0.3)
2023-05-23 pcb avec tracks à 5 mm
2023-05-23 PCB V3 VRAIMENT FINI
2023-05-23 pcb fini
2023-05-30 Update README.md
    introduction
2023-05-30 ajout des problèmes sur les PCBs
2023-06-05 impact environnemental
2023-06-06 final
2023-06-09 Update README.md partie alim et questions de dvpt durable
2023-06-09 Update README.md
    Description de la partie développement/logiciel complétée
2023-06-09 ajout d'information sur l'alimentation
2023-06-09 Rename [CoHoMa] Beacon Software Architecture.drawio to [CoHoMa]BeaconSoftwareArchitecture.drawio
